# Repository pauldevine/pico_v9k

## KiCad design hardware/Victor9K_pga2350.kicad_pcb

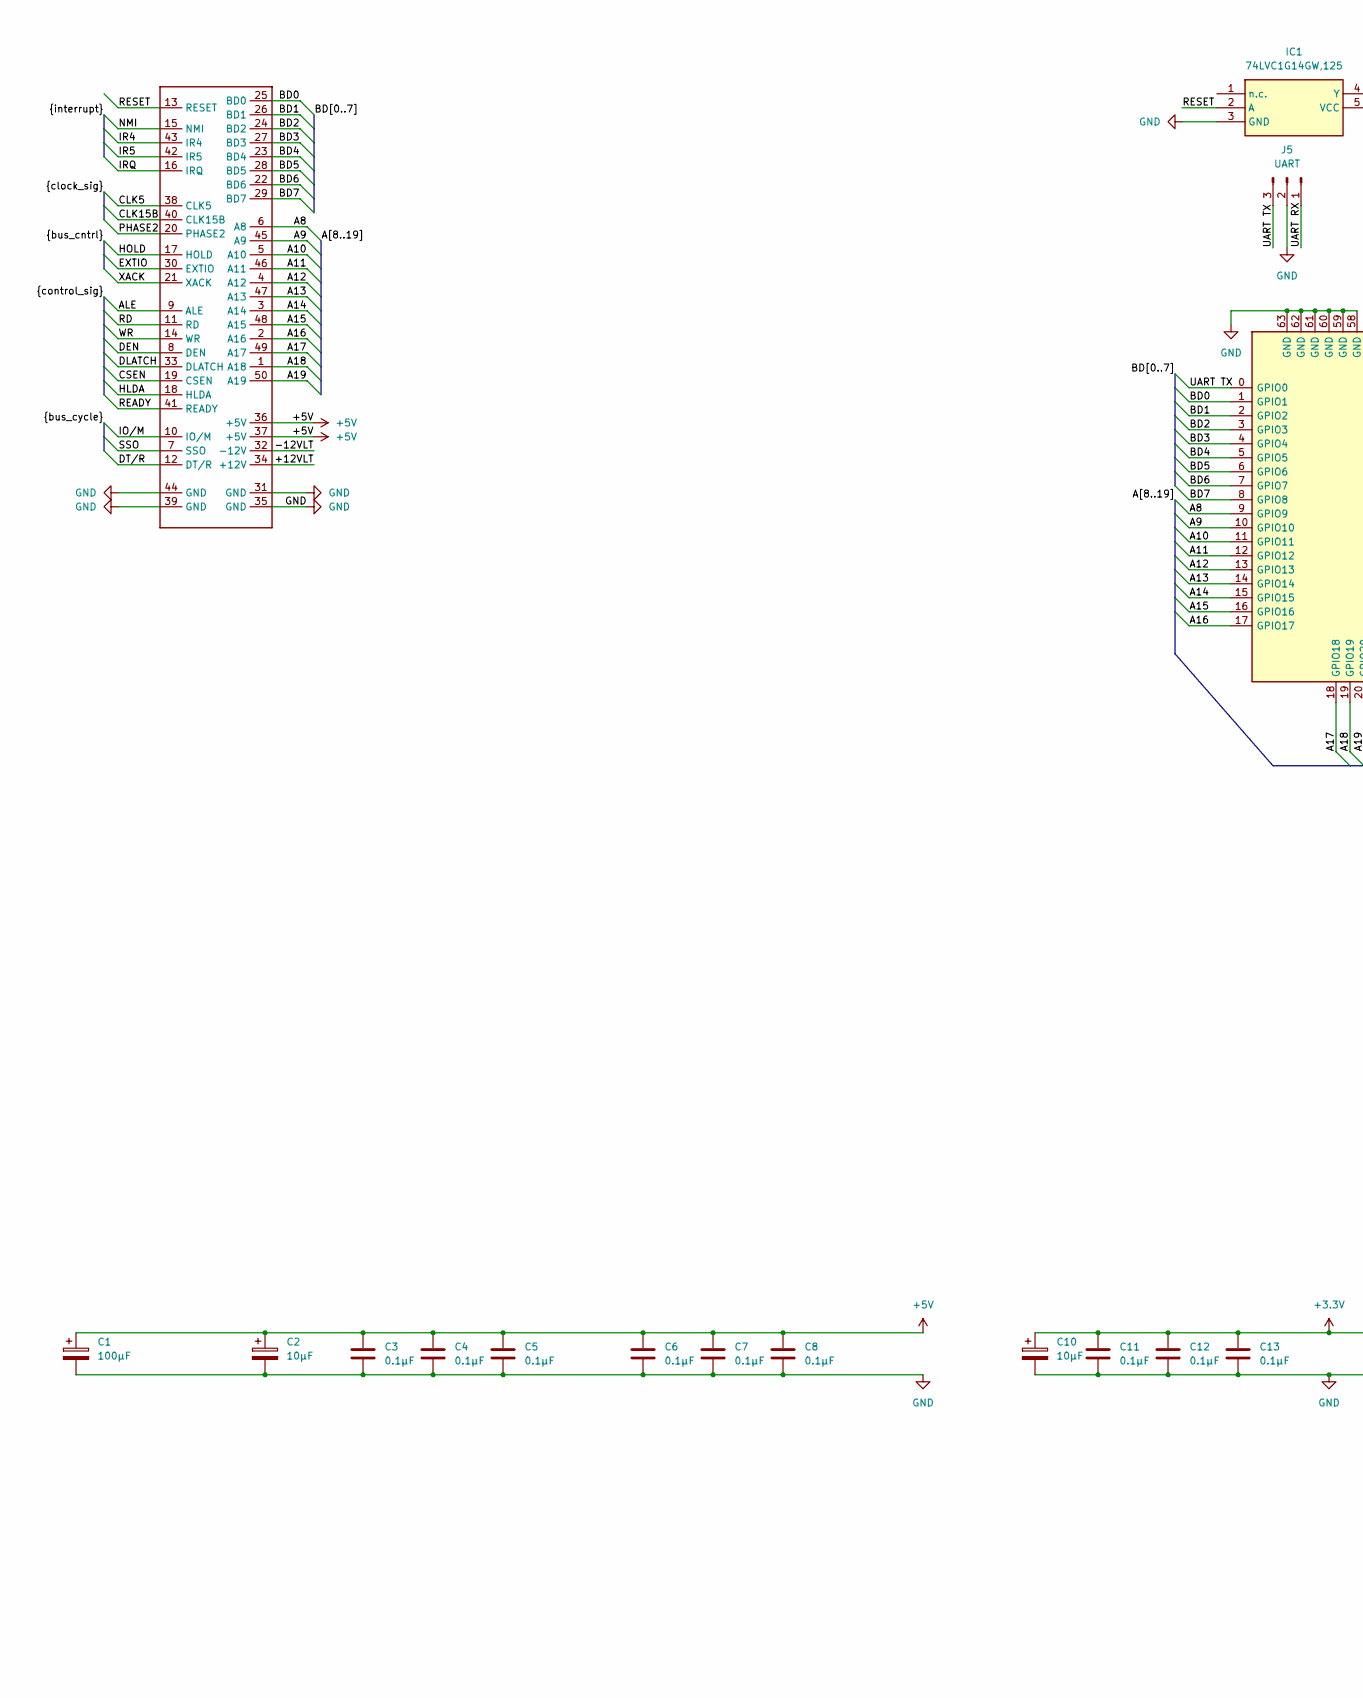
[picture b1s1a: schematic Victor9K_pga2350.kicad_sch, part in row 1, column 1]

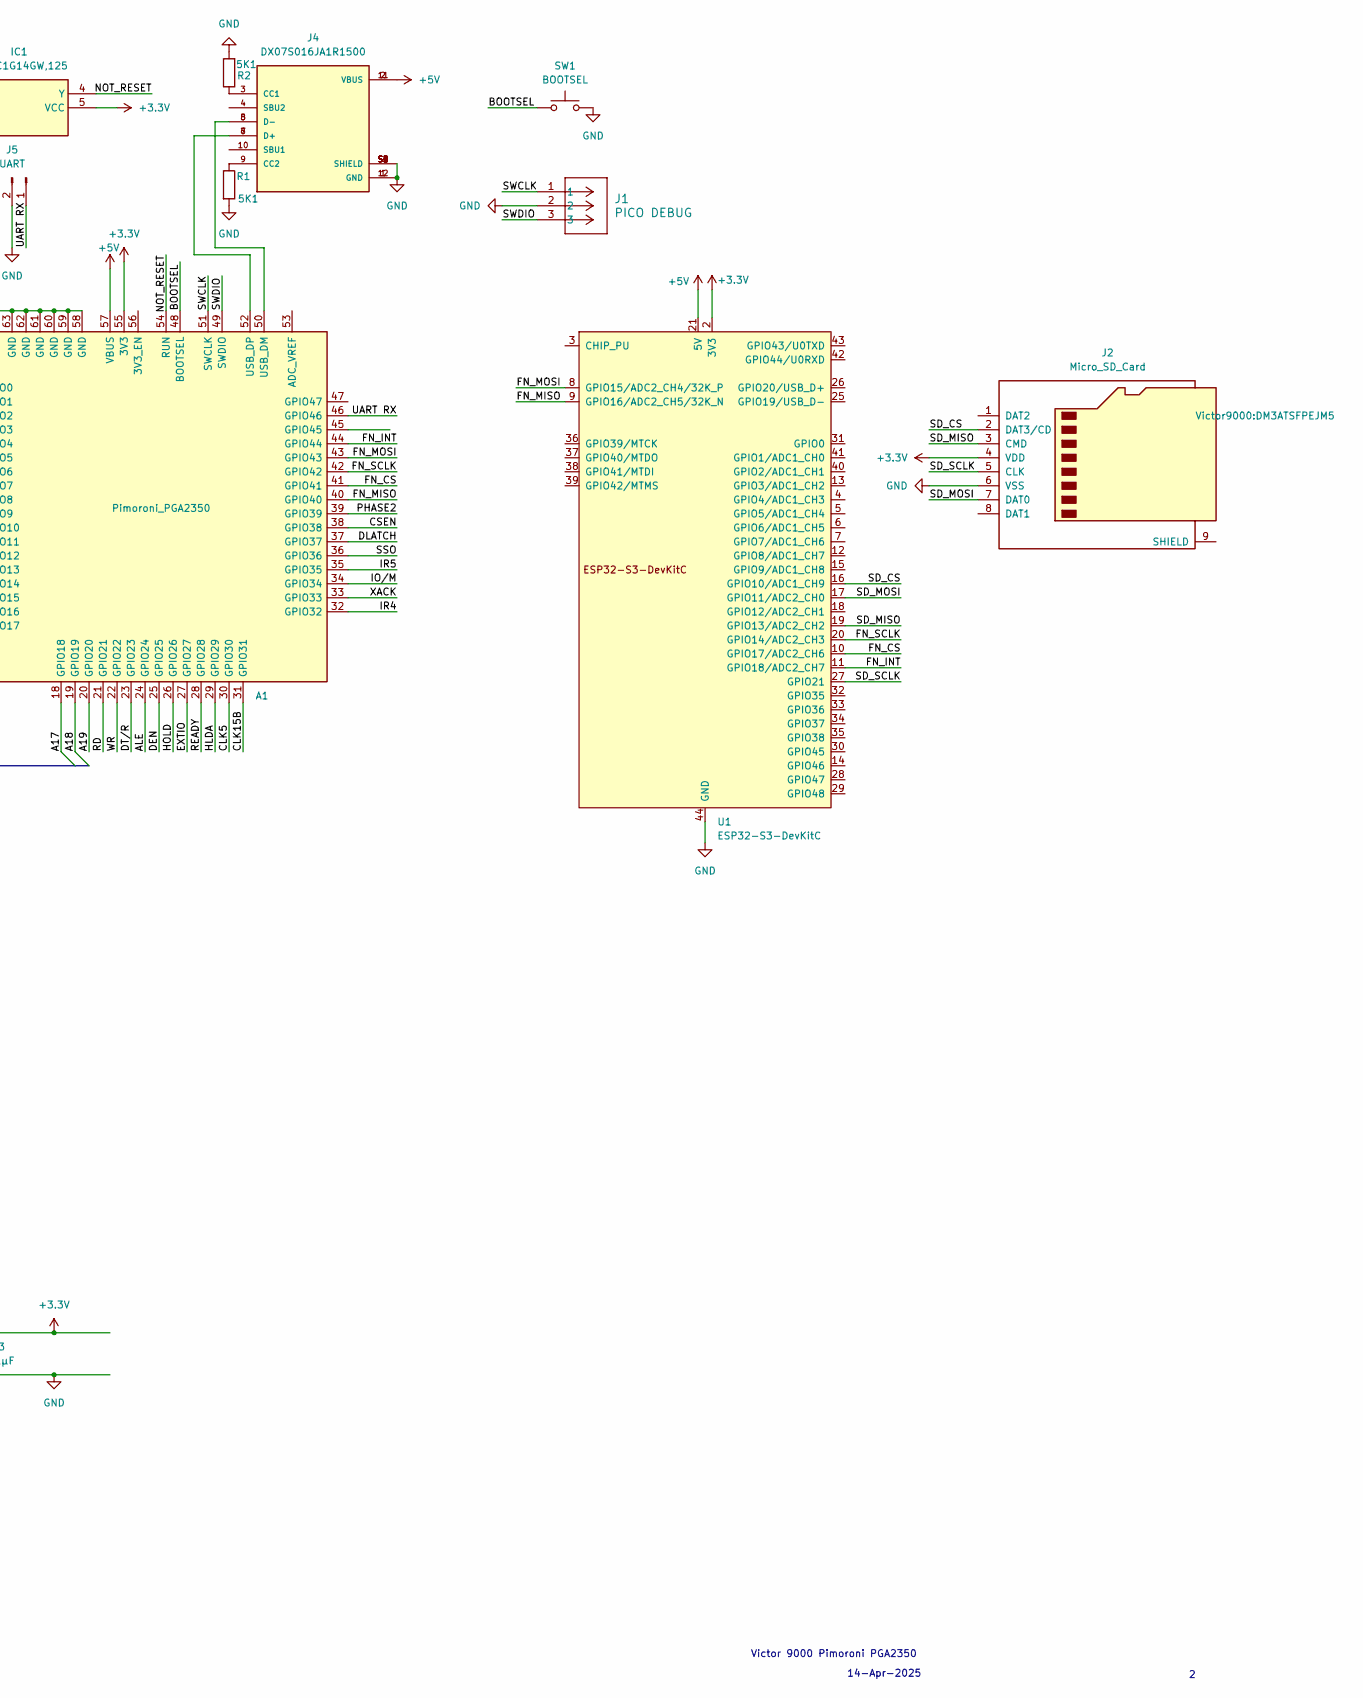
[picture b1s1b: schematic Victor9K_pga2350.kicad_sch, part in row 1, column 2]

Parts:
A1: Pimoroni_PGA2350; pimoroni_pga2350
C1: 100µF; CP_Axial_L11.0mm_D8.0mm_P15.00mm_Horizontal
C2, C10: 10µF; C_Disc_D5.0mm_W2.5mm_P5.00mm
C3, C4, C5, C6, C7, C8, C11, C12, C13: 0.1µF; C_Disc_D5.0mm_W2.5mm_P5.00mm
GF1: Victor 9K Expansion Port; Victor_Gold_Fingers_3
IC1: 74LVC1G14GW,125; SOT65P212X110-5N; Mouser Part Number 771-74LVC1G14GW-G
J1: PICO DEBUG; CONN_BM03B-SRSS-TBLFSN_JST
J2: Micro_SD_Card; DM3ATSFPEJM5
J4: DX07S016JA1R1500; JAE_DX07S016JA1R1500; PARTREV 1; JLCPCB Part # C3197885
J5: UART; PinHeader_1x03_P2.54mm_Vertical
R1, R2: 5K1; R_Axial_DIN0204_L3.6mm_D1.6mm_P5.08mm_Horizontal
SW1: BOOTSEL; B3FS1010P
U1: ESP32-S3-DevKitC

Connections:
+3.3V: A1.55 (3V3), C10.1, C11.1, C12.1, C13.1, IC1.5 (VCC), J2.4 (VDD), U1.1 (3V3), U1.2 (3V3)
+5V: A1.57 (VBUS), C1.1, C2.1, C3.1, C4.1, C5.1, C6.1, C7.1, C8.1, GF1.36 (+5V), GF1.37 (+5V), J4.2 (VBUS), J4.11 (VBUS), U1.21 (5V)
/+12VLT: GF1.34 (+12V)
/-12VLT: GF1.32 (-12V)
/A8: A1.9 (GPIO9), GF1.6 (A8)
/A9: A1.10 (GPIO10), GF1.45 (A9)
/A10: A1.11 (GPIO11), GF1.5 (A10)
/A11: A1.12 (GPIO12), GF1.46 (A11)
/A12: A1.13 (GPIO13), GF1.4 (A12)
/A13: A1.14 (GPIO14), GF1.47 (A13)
/A14: A1.15 (GPIO15), GF1.3 (A14)
/A15: A1.16 (GPIO16), GF1.48 (A15)
/A16: A1.17 (GPIO17), GF1.2 (A16)
/A17: A1.18 (GPIO18), GF1.49 (A17)
/A18: A1.19 (GPIO19), GF1.1 (A18)
/A19: A1.20 (GPIO20), GF1.50 (A19)
/ALE: A1.24 (GPIO24), GF1.9 (ALE)
/BD0: A1.1 (GPIO1), GF1.25 (BD0)
/BD1: A1.2 (GPIO2), GF1.26 (BD1)
/BD2: A1.3 (GPIO3), GF1.24 (BD2)
/BD3: A1.4 (GPIO4), GF1.27 (BD3)
/BD4: A1.5 (GPIO5), GF1.23 (BD4)
/BD5: A1.6 (GPIO6), GF1.28 (BD5)
/BD6: A1.7 (GPIO7), GF1.22 (BD6)
/BD7: A1.8 (GPIO8), GF1.29 (BD7)
/BOOTSEL: A1.48 (BOOTSEL), SW1.1
/CLK5: A1.30 (GPIO30), GF1.38 (CLK5)
/CLK15B: A1.31 (GPIO31), GF1.40 (CLK15B)
/CSEN: A1.38 (GPIO38), GF1.19 (CSEN)
/DEN: A1.25 (GPIO25), GF1.8 (DEN)
/DLATCH: A1.37 (GPIO37), GF1.33 (DLATCH)
/DT/R: A1.23 (GPIO23), GF1.12 (DT/R)
/EXTIO: A1.27 (GPIO27), GF1.30 (EXTIO)
/FN_CS: A1.41 (GPIO41), U1.10 (GPIO17/ADC2_CH6)
/FN_INT: A1.44 (GPIO44), U1.11 (GPIO18/ADC2_CH7)
/FN_MISO: A1.40 (GPIO40), U1.9 (GPIO16/ADC2_CH5/32K_N)
/FN_MOSI: A1.43 (GPIO43), U1.8 (GPIO15/ADC2_CH4/32K_P)
/FN_SCLK: A1.42 (GPIO42), U1.20 (GPIO14/ADC2_CH3)
/HLDA: A1.29 (GPIO29), GF1.18 (HLDA)
/HOLD: A1.26 (GPIO26), GF1.17 (HOLD)
/IO/M: A1.34 (GPIO34), GF1.10 (IO/M)
/IR4: A1.32 (GPIO32), GF1.43 (IR4)
/IR5: A1.35 (GPIO35), GF1.42 (IR5)
/IRQ: GF1.16 (IRQ)
/NMI: GF1.15 (NMI)
/NOT_RESET: A1.54 (RUN), IC1.4 (Y)
/PHASE2: A1.39 (GPIO39), GF1.20 (PHASE2)
/RD: A1.21 (GPIO21), GF1.11 (RD)
/READY: A1.28 (GPIO28), GF1.41 (READY)
/RESET: GF1.13 (RESET), IC1.2 (A)
/SD_CS: J2.2 (DAT3/CD), U1.16 (GPIO10/ADC1_CH9)
/SD_MISO: J2.3 (CMD), U1.19 (GPIO13/ADC2_CH2)
/SD_MOSI: J2.7 (DAT0), U1.17 (GPIO11/ADC2_CH0)
/SD_SCLK: J2.5 (CLK), U1.27 (GPIO21)
/SSO: A1.36 (GPIO36), GF1.7 (SSO)
/SWCLK: A1.51 (SWCLK), J1.1
/SWDIO: A1.49 (SWDIO), J1.3
/UART RX: A1.46 (GPIO46), J5.1
/UART TX: A1.0 (GPIO0), J5.3
/WR: A1.22 (GPIO22), GF1.14 (WR)
/XACK: A1.33 (GPIO33), GF1.21 (XACK)
GND: A1.58 (GND), A1.59 (GND), A1.60 (GND), A1.61 (GND), A1.62 (GND), A1.63 (GND), C1.2, C2.2, C3.2, C4.2, C5.2, C6.2, C7.2, C8.2, C10.2, C11.2, C12.2, C13.2, GF1.31 (GND), GF1.35 (GND), GF1.39 (GND), GF1.44 (GND), IC1.3 (GND), J1.2, J2.6 (VSS), J4.1 (GND), J4.12 (GND), J4.S1 (SHIELD), J4.S2 (SHIELD), J4.S3 (SHIELD), J4.S4 (SHIELD), J4.S5 (SHIELD), J4.S6 (SHIELD), J5.2, R1.2, R2.2, SW1.2, U1.22 (GND), U1.23 (GND), U1.24 (GND), U1.44 (GND)
unnamed: A1.50 (USB_DM), J4.5 (D-), J4.8 (D-)
unnamed: A1.52 (USB_DP), J4.6 (D+), J4.7 (D+)
unnamed: J4.3 (CC1), R2.1
unnamed: J4.9 (CC2), R1.1

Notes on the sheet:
14-Apr-2025
Victor 9000 Pimoroni PGA2350

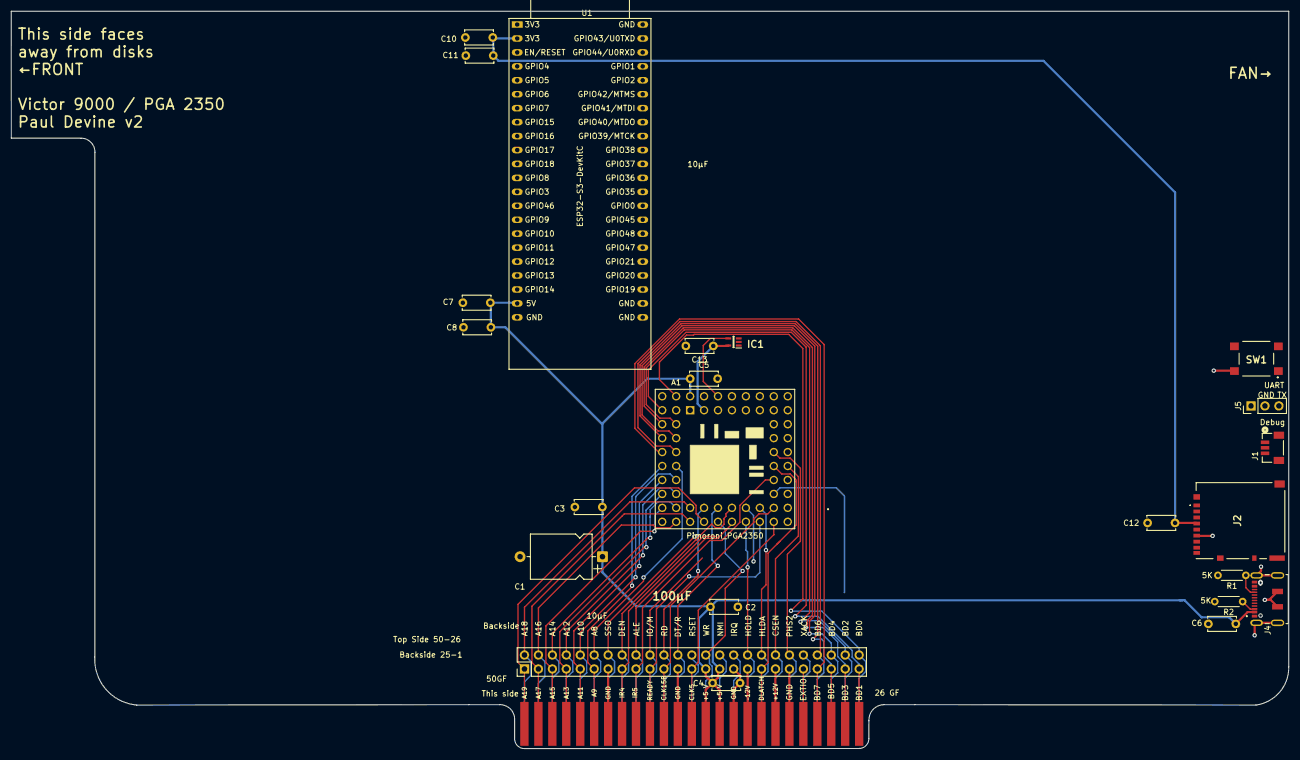
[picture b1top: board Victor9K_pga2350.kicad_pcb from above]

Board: 4 copper layers, 232.7 x 134.3 mm, 23 parts (0 on the bottom side), 62 nets.

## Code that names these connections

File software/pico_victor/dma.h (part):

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#define RD_PIN 21
#define WR_PIN 22
#define DTR_PIN 23       
#define ALE_PIN 24      
#define HOLD_PIN 25
#define XACK_PIN 26
#define EXTIO_PIN 27
#define READY_PIN 28
#define HLDA_PIN 29
#define CLOCK_5_PIN 30
#define CLOCK_15B_PIN 31
#define IR_4_PIN 32
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#define DMA_IRQ_PIN IR_4_PIN
#define DMA_IRQ_ASSERT_LEVEL 1
#define DMA_IRQ_DEASSERT_LEVEL 0
#define SSO_PIN 36
#define DLATCH_PIN 37
#define CSEN_PIN 38
#define PHASE_2_PIN 39
#define DEN_PIN 40

// SD card SPI interface pins (hardware SPI1 on RP2350)
#define SD_CS_PIN   41  // Manual GPIO chip select -> SD DAT3/CS
#define SD_SCK_PIN  42  // SPI1_SCK              -> SD CLK
#define SD_MOSI_PIN 43  // SPI1_TX               -> SD CMD/DI
#define SD_MISO_PIN 44  // SPI1_RX               -> SD DAT0/DO
// GPIO 45, 46 are now free

#define UART_TX_PIN 0
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
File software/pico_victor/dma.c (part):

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}

// Safely restart the register PIO SM: disable, clear FIFOs, release
// XACK/EXTIO pindirs via NOP exec, restart SM at wrap_target, re-enable.
void reset_register_pio_sm(void) {
    pio_sm_set_enabled(PIO_REGISTERS, REG_SM_CONTROL, false);
    pio_sm_clear_fifos(PIO_REGISTERS, REG_SM_CONTROL);

    // Release XACK/EXTIO pindirs by executing a NOP with no side-set.
    // If the SM was mid-cycle with side S_XACK asserted, the frozen pindirs
    // would hold XACK low -> READY low -> DMA PIO hangs at wait READY.
    pio_sm_exec(PIO_REGISTERS, REG_SM_CONTROL, pio_encode_nop());
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}

static inline bool wait_for_hlda_assert(void) {
    return wait_for_pin_level(HLDA_PIN, true, make_timeout_time_us(DMA_TIMEOUT_US));
}

static inline bool wait_for_hlda_release(void) {
    return wait_for_pin_level(HLDA_PIN, false, make_timeout_time_us(DMA_TIMEOUT_US));
}

static inline void drive_pin_sio(uint pin, bool level) {
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        gpio_set_slew_rate(pin, GPIO_SLEW_RATE_SLOW);
        gpio_pull_down(pin); // enable pull-downs
        gpio_put(pin, 0);  // by default drive low
        gpio_set_dir(pin, GPIO_IN); // set as output to assert HOLD/
        
        //printf("ontime gpio_setup %d  ", pin);
    }
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    // we need to set appropriate pull-ups or pull-downs
    // we defaulted everything to pull low above, so just need to fix the active low pins

    gpio_pull_down(ALE_PIN);  // ALE is active high, so pull-down
    gpio_set_drive_strength(ALE_PIN, GPIO_DRIVE_STRENGTH_12MA);   //ALE has a pulldown bias externally on the board, drive it higher.

    gpio_pull_up(RD_PIN);   // RD is active low, so pull-up
    gpio_pull_up(WR_PIN);   // WR is active low, so pull-up
    gpio_pull_up(DTR_PIN);  // DTR is active low, so pull-up 
    gpio_pull_up(DEN_PIN);  // DEN is active low, so pull-up
    gpio_pull_up(SSO_PIN);  // SSO is active low, so pull-up
    gpio_pull_up(DLATCH_PIN); // DLATCH is active low, so pull-up
    gpio_pull_up(EXTIO_PIN); // EXTIO is active low, so pull-up
    gpio_pull_up(XACK_PIN);  // XACK is active low (open-drain), so pull-up
    gpio_disable_pulls(HOLD_PIN);  //HOLD has a pullup on the motherboard

    // DMA IRQ line: drive low by default, assert when interrupts are pending.
    gpio_set_function(DMA_IRQ_PIN, GPIO_FUNC_SIO);
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    // These only touch PIO1's registers — no effect on pads yet because
    // pin functions are still PIO0.
    uint32_t ctrl_high_mask = (1u << RD_PIN) | (1u << WR_PIN) |
                              (1u << DTR_PIN) | (1u << EXTIO_PIN);
    uint32_t ctrl_out_mask  = ctrl_high_mask | (1u << ALE_PIN);

    // Output values: RD/=1, WR/=1, DTR/=1, EXTIO/=1 (inactive), ALE=0 (no latch)
    pio_sm_set_pins_with_mask(PIO_DMA_MASTER, DMA_SM_CONTROL,
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    pio_gpio_init(PIO_DMA_MASTER, WR_PIN);
    gpio_set_function(DTR_PIN, function);
    pio_gpio_init(PIO_DMA_MASTER, DTR_PIN);
    gpio_set_function(ALE_PIN, function);
    pio_gpio_init(PIO_DMA_MASTER, ALE_PIN);
    gpio_set_function(EXTIO_PIN, function);
    pio_gpio_init(PIO_DMA_MASTER, EXTIO_PIN);

    // PHASE 3: Now safe to set up address/data pins — control signals
    // are already actively driven to safe levels.
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        pio_sm_set_pins_with_mask(PIO_DMA_MASTER, DMA_SM_CONTROL, 0u, 1u << pin);
    }

    // Address pins as outputs (safe: ALE=LOW prevents spurious latch)
    pio_sm_set_consecutive_pindirs(PIO_DMA_MASTER, DMA_SM_CONTROL,
                                   BD0_PIN, ADDRESS_BUS_SIZE, true);

    // DEN is at GPIO 40 (outside PIO's 0-31 range), use plain GPIO.
    // DEN is not needed for DMA — hold inactive (high).
    gpio_init(DEN_PIN);
    gpio_put(DEN_PIN, 1);
    gpio_set_dir(DEN_PIN, GPIO_OUT);

    // Input pins: READY, CLK5, CLK15B
    setup_pin_dma_control(READY_PIN, GPIO_IN, 0);
    setup_pin_dma_control(CLOCK_5_PIN, GPIO_IN, 0);
    setup_pin_dma_control(CLOCK_15B_PIN, GPIO_IN, 0);

    gpio_init(SSO_PIN);
    gpio_put(SSO_PIN, 0);
    gpio_set_dir(SSO_PIN, GPIO_OUT);

    gpio_init(IO_M_PIN);
    gpio_put(IO_M_PIN, 0);
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
    // Explicitly release XACK by switching it to SIO/input during DMA.
    // XACK stays on PIO0 function otherwise (not in the BD0..ALE range),
    // and frozen PIO0 pindirs could hold XACK low -> READY low -> DMA hangs.
    gpio_init(XACK_PIN);
    gpio_set_dir(XACK_PIN, GPIO_IN);
}

static inline void park_dma_release_control_pins_on_sio(void) {
    // Keep the high-risk strobes actively parked while HOLD is still asserted.
    // This shrinks the float window that the external RC network has to absorb.
    drive_pin_sio(ALE_PIN, 0);
    drive_pin_sio(RD_PIN, 1);
    drive_pin_sio(WR_PIN, 1);
    drive_pin_sio(DTR_PIN, 1);
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        gpio_set_function(pin, reg_function);
    }

    // Restore the rest of the register-bus pins now.  ALE/RD/WR/DT/R stay on
    // SIO until HLDA drops so they never float during the hand-back.
    for (int pin = XACK_PIN; pin <= CLOCK_15B_PIN; ++pin) {
        if (pin == HOLD_PIN || pin == HLDA_PIN) {
            continue;
        }
        gpio_set_function(pin, reg_function);
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    gpio_set_function(IO_M_PIN, GPIO_FUNC_SIO);
    gpio_set_dir(IO_M_PIN, GPIO_IN);

    gpio_set_dir(SSO_PIN, GPIO_IN);
    gpio_set_dir(DEN_PIN, GPIO_IN);
}

static inline void finish_register_pio_handoff_locked(void) {
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    // Return the CPU strobes to the register listener while HOLD is still
    // asserted.  Driving them with SIO all the way until HLDA falls can fight
    // the 8088's first resumed bus cycle.
    gpio_set_function(ALE_PIN, reg_function);
    gpio_set_function(RD_PIN, reg_function);
    gpio_set_function(WR_PIN, reg_function);
    gpio_set_function(DTR_PIN, reg_function);
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    // touching the DMA SM.  HOLD remains asserted throughout this phase.
    park_dma_release_control_pins_on_sio();

    gpio_set_dir(ALE_PIN, GPIO_OUT);
    gpio_put(ALE_PIN, 0);

    pio_sm_set_enabled(PIO_DMA_MASTER, DMA_SM_CONTROL, false);
    pio_sm_clear_fifos(PIO_DMA_MASTER, DMA_SM_CONTROL);
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
    // HOLD/ is open-drain on the Victor side, so releasing direction is the
    // safe equivalent of deasserting it high.
    gpio_set_dir(HOLD_PIN, GPIO_IN);

    if (!wait_for_hlda_release()) {
        fast_log("%s: HLDA release TIMEOUT after HOLD release\n", context);
    }
    //turn off constant current sink for ALE
    gpio_set_dir(ALE_PIN, GPIO_IN);
}


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}

// DMA error codes for sasi_log_dma_error()
#define DMA_ERR_MASTER_FAIL  0xF0  // Failed to obtain DMA bus master (clock/HLDA timeout)
#define DMA_ERR_PIO_TIMEOUT  0xF1  // PIO SM stuck during DMA transfer

// Emergency abort: force-release DMA master and clean up PIO state.
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        return false;
    }

    gpio_init(HOLD_PIN);
    gpio_put(HOLD_PIN, 0);  // sink the line, HOLD/ is open drain on Victor
    gpio_set_dir(HOLD_PIN, GPIO_OUT); // set as output to assert HOLD/
    gpio_init(HLDA_PIN);
    gpio_set_dir(HLDA_PIN, GPIO_IN);

    if (!wait_for_hlda_assert()) {
        gpio_set_dir(HOLD_PIN, GPIO_IN); // release HOLD on timeout
        return false;
    }

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    uint32_t obtain_elapsed = (uint32_t)(time_us_64() - t0_obtain);
    sasi_op_record(obtain_elapsed, &sasi_op_timing.max_obtain_us,
                   SASI_OP_OBTAIN, dma_registers.dma_address.full >> 9);
    // Release XACK/EXTIO pindirs before disabling register SM.
    // If the SM is mid-cycle with side S_XACK asserted, the frozen pindirs
    // would hold XACK low -> READY low -> DMA PIO hangs at wait READY.
    pio_sm_exec(PIO_REGISTERS, REG_SM_CONTROL, pio_encode_nop());
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    }

    // Assert HOLD/ (open-drain)
    gpio_init(HOLD_PIN);
    gpio_put(HOLD_PIN, 0);
    gpio_set_dir(HOLD_PIN, GPIO_OUT);
    gpio_init(HLDA_PIN);
    gpio_set_dir(HLDA_PIN, GPIO_IN);

    if (!wait_for_hlda_assert()) {
        gpio_set_dir(HOLD_PIN, GPIO_IN);  // release on timeout
        return false;
    }
    return true;
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
// Release HOLD/ so the 8088 resumes execution.
void release_victor_bus(void) {
    gpio_set_dir(HOLD_PIN, GPIO_IN);  // float high via pull-up
}

// Handle SASI REQ signal and DMA transfers (based on MAME ctrl_change_handler)
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
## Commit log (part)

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2025-09-13 empty start
2025-09-13 cleaning up initial import
2025-09-15 updated CLAUDE.md for new project layout.
2025-09-15 SPI-backed disk reads
2025-09-15 added on-device test harness
2025-09-19 renamed SCSI to SASI, initial fujinet payload interaction adjustments
2025-09-21 cleaned up fujinet protocol adaptation
2025-09-21 cleaning up SPI handshaking
2025-09-21 cleaning up SPI interface, fixing mount process
2025-09-22 increase SPI timeout to account for slow actions like disk mounting
2025-09-25 renaming claude.md to agents.md
2025-09-25 cleaning up UART for actual hardware
2025-09-25 added spi_end_transaction_phase()
2025-09-25 moved back to 115K baud
2025-09-26 updating pico code to correctly handle LBA
2025-09-27 initial cleanup of gpio state all managed in pio land
2025-09-27 added local documentation to help with context
2025-09-28 bunch of debugging changes
2025-09-28 initial version trying to benchmark
2025-09-28 after debugging dma_ultra_fast.c
2025-09-28 adjusting register control bits
2025-09-28 adding debug queue
2025-10-02 added a bumch of tests
2025-10-02 cleaning up .pio code during debug
2025-10-02 initial stab at removing 74LVC245 chips
2025-10-03 updated the pio files to remove refernces to the 74LVC245s
2025-10-03 removed 74LVC245 from test dma diagnostic
2025-10-05 iterating on pio approach without 74LVC245s
2025-10-07 updating Claude.md
2025-10-07 moved to mov pindirs ~null instead of specific attributes
2025-10-10 correcting bit manipulation to create pio input
2025-10-10 semi-broken state before looking at isolating side-set to pindirs situation
2025-10-11 moved data byte to y register so mov pindirs, ~null could blow away OSR without side effect
2025-10-11 added dump_pio_dbg() to debug what's up with the pio instance
2025-10-11 iterating on why the pio routing isn't working
2025-10-11 Updated PIO GPIO routing instructions
2025-10-11 chatgpt wrote a nice overview of the technical details of the project
2025-10-11 initial version with read partially working
2025-10-11 Updated the control-register bit masks to match the Victor BIOS definitions
2025-10-11 adjusted sideset bit values, seeing output again
2025-10-12 playing with HLDA initialization
2025-10-12 removing outdated comments
2025-10-13 removed pre-loading of x as read/write flag. instead added to payload
2025-10-13 updated log output
2025-10-13 adjust ALE to align to CLOCK_15B
2025-10-13 first version that has a READ success. Changed output for A8-A19 stability during T3
2025-10-13 moving all the code to 2 FIFO entries per DMA call
2025-10-13 read still working, extended T4, still no go on write
2025-10-13 first naked rp2350 reads and write working!
2025-10-14 deleted cruft tests, updated Claude.md, fixed register values in test/dos_dma_test/dmatest.c
2025-10-14 fixed state machine change from separate wr/rd instances to one common sm
2025-10-14 updated board_registers.pio for new pin layout on 74LVC245-free naked rp2350 board
2025-10-14 updated pio instance handling for registers and dma_read_write to switch functions between usage
2025-10-15 updated Claude.md for latest
2025-10-15 updated timing to account for T4
2025-10-16 cleaning up single sm instead of 2
2025-10-17 before deferring work for faster register access, reads currently failing
2025-10-17 initial version of dma_board_cached, adjusted pio RD cycle hold time, first time victor sees some data correctly. still big timing issue with PIO
2025-10-18 added minimalist memory test
2025-10-18 fixed minimal test build issues
2025-10-19 updated DOS tests
2025-10-20 added single register read/write test
2025-10-20 updated Claude.md with latest status
2025-10-21 mid swing debugging BD0-BD7 not populating in dma_registers, hardcoded some test values
2025-10-25 initial version testing starting with GPIO1
2025-10-26 dma_read_write pio sm disabled, have hardcoded output from board_registers appearing on data pins bd0-bd7
2025-11-01 setting GPIO_DRIVE_STRENGTH_12MA on gpio pins
2025-11-01 turning jmp for address back on
2025-11-04 initial version with EXTIO added, hardcoded 0xFF working correcltly for the 1st time
2025-11-04 removed hard coded response and fast_log() in the middle of the hot path
2025-11-04 trying to extend RD sample on extio.pio to resolve timing race condition
2025-11-05 first time passing all tests, lowere GPIO_DRIVE_STRENGTH to 2MA, added delay to board_registers
2025-11-05 initial thought on moving OUT instructions to 1 state machine
2025-11-08 created IO/M helper to free up a lower 32 pin
2025-11-08 added introduction to the Victor hardware
2025-11-08 renamed directory
2025-11-08 Add comprehensive PIO state machine coordination diagrams
    Created detailed mermaid sequence diagrams showing T-state timing and
    signaling between board_registers, dma_read_write, and bus_output_helper
    state machines.
    Diagrams cover:
    - Register read cycles (8088 reading from 0xEF300)
    - DMA read cycles (Pico reading from 8088 memory)
2025-11-08 Add comprehensive ARM-PIO integration analysis for bus_output_helper
    Detailed analysis of required ARM-side code changes to support the new
    three-state-machine PIO architecture.
    Key findings:
    - ARM IRQ handlers must push register read responses to bus_output_helper
    TX FIFO instead of board_registers TX FIFO
    - 800ns READY timing window is sufficient for ARM response (~750-850ns)
2025-11-08 added bus_output_helper.pio to the cmake configuration
2025-11-08 Add bus_output_helper.pio header generation to CMakeLists.txt
    Added pico_generate_pio_header calls for bus_output_helper.pio to both
    dma_board and dma_board_cached targets. This was the missing piece that
    prevented compilation.
    Without this, the #include "bus_output_helper.pio.h" in dma_board.c
    would fail to find the generated header file.
2025-11-10 cleanup after changing around payload for helper situation, still WIP
2025-11-10 Fix board_registers payload address extraction to match PIO format
    The board_registers.pio state machine uses right-shift ISR config,
    which places the 20-bit address in bits [29:10] with the 2-bit payload
    type in bits [31:30]. The helper functions were incorrectly extracting
    from bits [19:0].
    Changes:
    - Fix dma_fifo_prefetch_address() to extract from bits [29:10]
2025-11-10 cleaning up T3_WRITE address values
2025-11-10 Revert WRITE payload to correct format after board_registers.pio fix
    The addition of `mov isr, osr` at board_registers.pio:66 changes the
    WRITE payload format by restoring the original address position before
    the data and type shifts occur.
    With line 66 fix, WRITE path is:
    1. Line 66: mov isr, osr -> ISR = [addr:31-12][zeros:11-0]
    2. Line 67: in pins, 8 -> ISR = [data:31-24][addr:23-4][zeros:3-0]
2025-11-11 added debug for bus helper
2025-11-11 removed inappropriate pre-fecth decrement, not used in write situation
2025-11-11 reworked bus_output_helper.pio, renamded board_regsiters.pio program identifier. WIP
2025-11-11 changed pico_victor/dma_read_write.pio to wait on IRQ instead of pull block
2025-11-11 Restructure IRQ handlers for separate PIO programs
    Created separate IRQ handler functions for board_registers and
    bus_output_helper PIO programs to align with the new PIO organization
    where each PIO handles specific payload types:
    - board_registers_irq_handler_cached_asm(): Handles WRITE_VALUE payloads
    from board_registers (PIO0/SM0)
    - bus_output_helper_irq_handler_cached_asm(): Handles PREFETCH payloads
2025-11-11 Remove push instructions from board_registers.pio T3_READ
    The new IRQ handler architecture splits responsibilities:
    - board_registers handler: Only processes WRITE_VALUE payloads
    - bus_output_helper handler: Processes PREFETCH and DMA_READ payloads
    This change removes the PREFETCH and READ_COMMIT push instructions
    from board_registers.pio T3_READ section, so board_registers only
    pushes WRITE_VALUE payloads from T3_WRITE. The PREFETCH push now
2025-11-12 Fix remaining payload flag inconsistencies
    This commit addresses the last inconsistencies in the payload flag
    refactoring from the old PREFETCH/COMMIT two-phase protocol to the
    new single-phase REG_READ protocol.
    Changes:
    - dma.h: Fix board_fifo_encode_read() to use FIFO_REG_READ (0x00)
    instead of FIFO_DMA_READ (0x02)
2025-11-12 Update Claude.md with latest PIO restructuring status (nov-12)
2025-11-14 fixed payload mapping, clarified method naming, cleaned up pio FIFO relationships, fixed bus_ouput_helper missing initialization
2025-11-14 Fix sideset pin initialization order in bus_output_helper
    The sideset pin (HOLD_PIN) was not appearing on logic analyzer because
    GPIO initialization was happening before pio_sm_init(), which resets
    the state machine and clears pin configurations.
    Changes:
    - Move all GPIO initialization (pio_gpio_init, pin values, pindirs) to
    occur AFTER pio_sm_init() is called
2025-11-15 Add example pio_shared.h for shared C/PIO constants
    This file demonstrates the recommended approach for sharing constant
    definitions between C code and PIO assembly programs using the C
    preprocessor. This addresses the code review finding about duplicate
    FIFO_* payload type constants across multiple files.
    This is a suggested refactoring, not yet integrated into the codebase.
2025-11-15 Refactor PIO state debug output for better diagnostics
    - Fixed incorrect API usage (was passing int instead of PIO pointer)
    - Added comprehensive state machine status for all 4 SMs:
    * board_registers (PIO0 SM0)
    * bus_output_helper (PIO1 SM0)
    * dma_read_write (PIO2 SM0)
    * iom_helper (PIO2 SM1)
2025-11-16 making progress debugging inter-pio irq passing
2025-11-16 fixing output challneges with board_registers_output timing and pindirs
2025-11-25 first version passing register tests after rewrite
2025-11-27 removed debugging side-set HOLD from board_registers_output.pio
2025-12-06 WIP iterating on getting DMA working in new both active setup, removing HOLD as side-set debug pin, not working yet
2025-12-06 removed old I/O_M sideset functionality from dma_rw_control.pio
2025-12-07 realized I was overflowing the PIO instruction limit and wasn't testing for that. added runtime checks
2025-12-14 further progress resovling contention with pio output parallelization
2025-12-24 fixes a few timing related bugs in the pio code
2025-12-24 initial start rewiring things to old pio with new arm
2025-12-27 debugging after big rewrite, fixed some gpio initialization, pio logic, payload values
2025-12-31 added some volatiles, additional debugs, attempting to fix boot process
2026-01-01 adding IRQ4 activation based on testing factoryf
2026-01-19 cleaning up hardware for new layout
2026-01-27 initial version of re-worked hardware removing the 74LVC245's
2026-01-27 some tools to help parse debug logs
2026-01-30 first version to successfully boot, only to onboard motherboard RAM, doesn't work with expansion RAM
2026-01-30 removed some debugging to eliminate serial delays
2026-01-31 psram logging branch, needs gpa2350 in hardware
2026-02-10 adding a boot sequence test
2026-02-13 saving branch with SASI logging working, but bus interactions unreliable
2026-02-15 fixing hd stress test to not have divide by zero error
2026-02-23 WIP continuing move to use XACK, fixed several bugs in intial implementation after testing. still not booting reliably, but now register reads are happening. current bug state points to mishandling S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
2026-02-24 WIP continuing move to use XACK, reworked SASI logging, adjusted SASI state transitions
2026-02-25 WIP fixed the boot process, SASI RESET was clobbering immediately following SASI command status changes. that's been corrected
2026-02-26 WIP saving broken state, booting not working, cleaned up ISR pressure by reorganizing core0 / core 1 ISR handling. reworked some SD card interactions
